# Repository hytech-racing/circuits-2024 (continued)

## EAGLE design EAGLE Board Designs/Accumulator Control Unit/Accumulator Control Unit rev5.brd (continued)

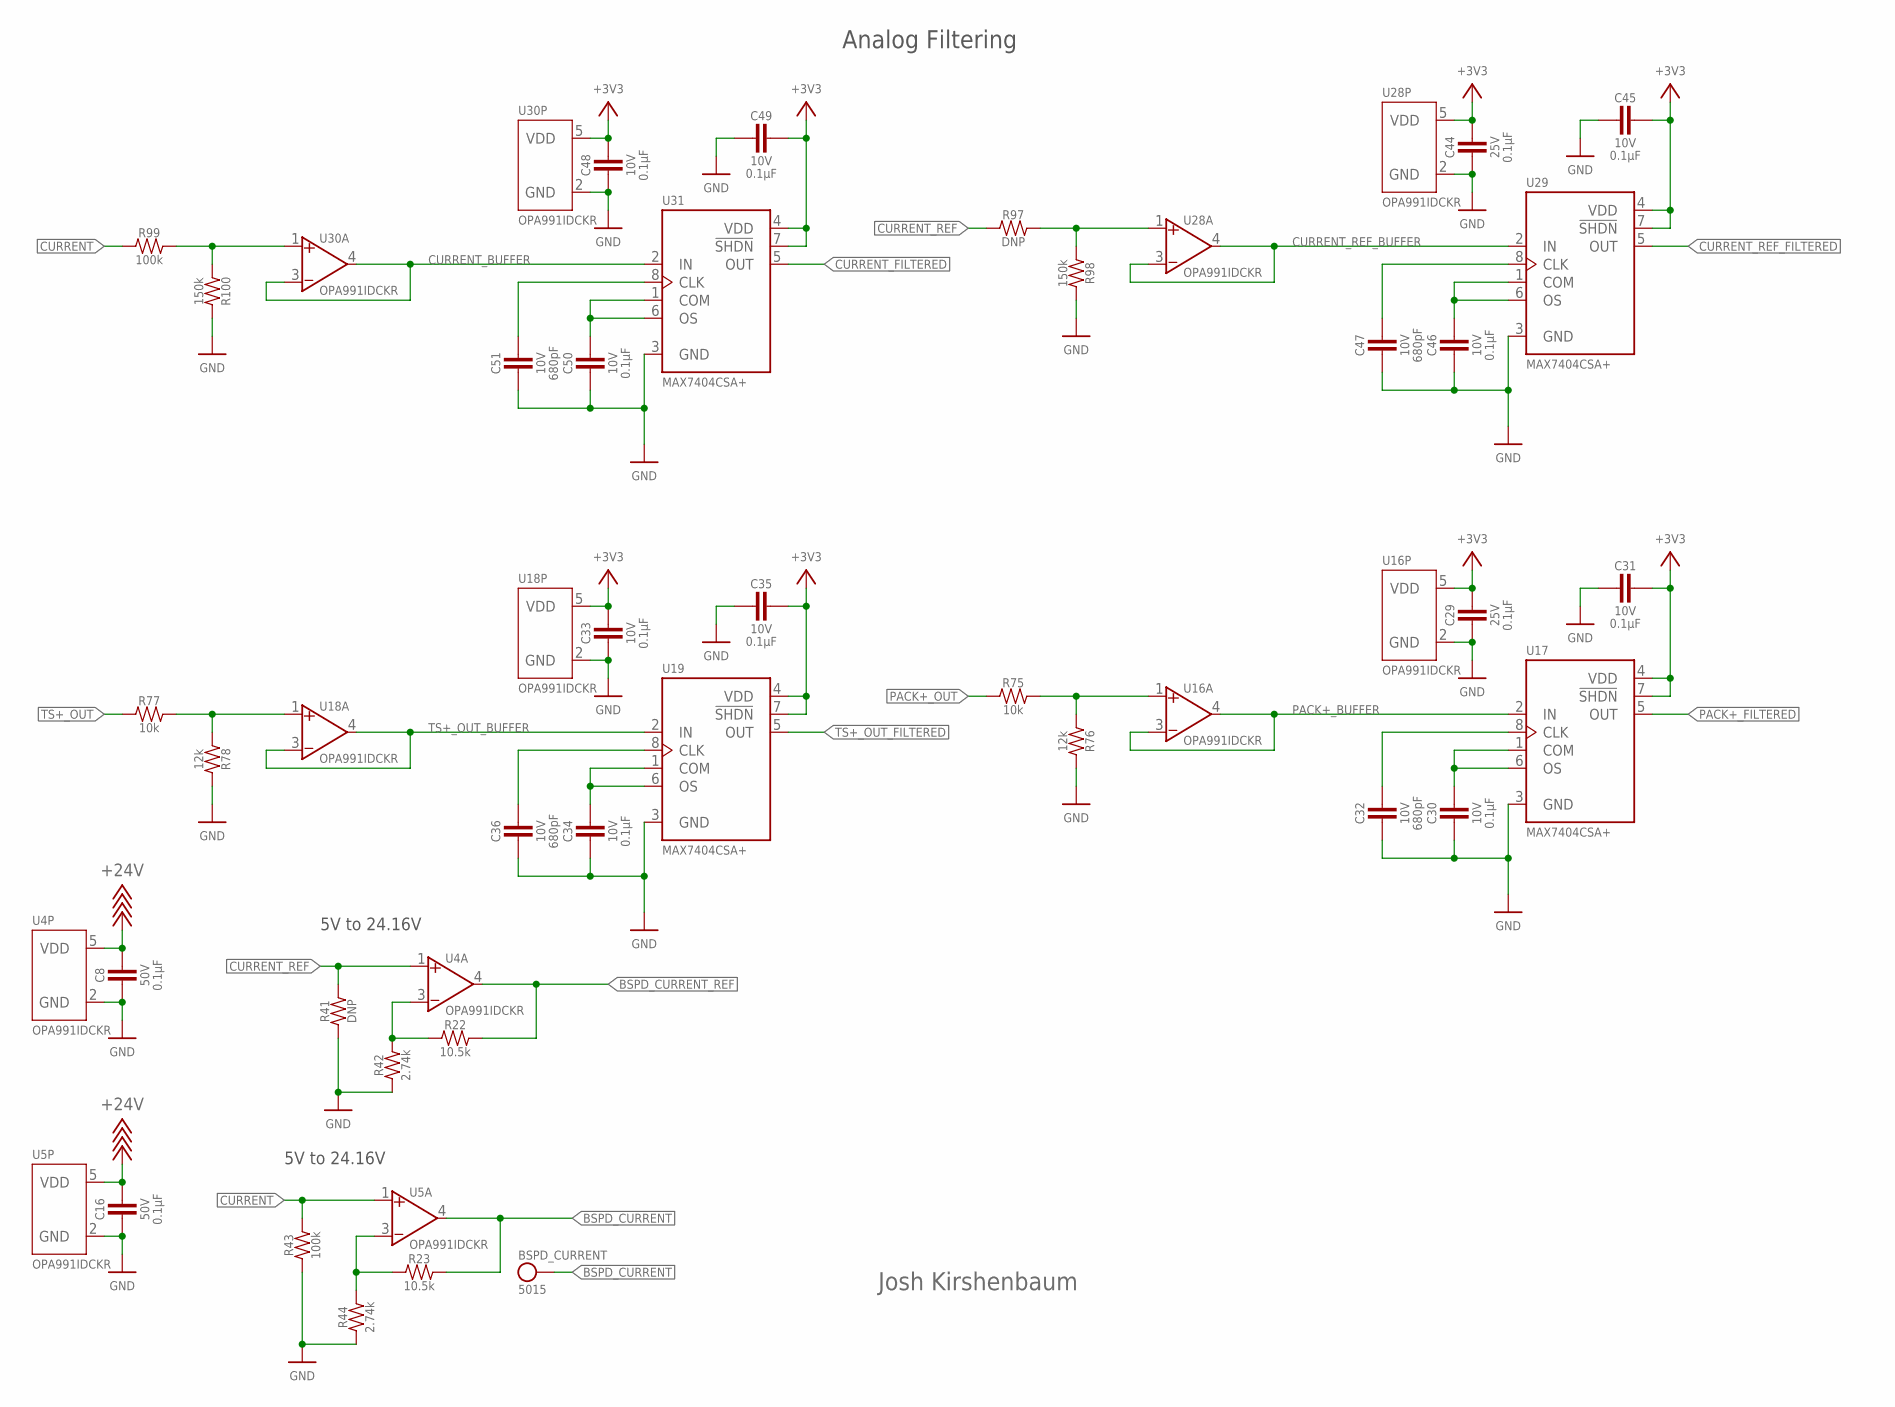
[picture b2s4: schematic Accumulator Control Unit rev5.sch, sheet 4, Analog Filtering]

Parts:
BSPD_CURRENT: TEST_POINT; MICRO_MINIATURE
C8, C16: CAPACITOR_0603_50V_0.1UF; 0603-CAP
C29, C44: CAPACITOR_0603_25V_0.1UF; 0603-CAP
C30, C31, C33, C34, C35, C45, C46, C48, C49, C50: CAPACITOR_0603_10V_0.1UF; 0603-CAP
C32, C36, C47, C51: CAPACITOR_0603_10V_680PF; 0603-CAP
R22, R23: RESISTOR_0603_10.5K; 0603-RES
R41, R97: RESISTOR_0603_DNP; 0603-RES
R42, R44: RESISTOR_0603_2.74K; 0603-RES
R43, R99: RESISTOR_0603_100K; 0603-RES
R75, R77: RESISTOR_0603_10K; 0603-RES
R76, R78: RESISTOR_0603_12K; 0603-RES
R98, R100: RESISTOR_0603_150K; 0603-RES
U4, U5, U16, U18, U28, U30: OPAMP_1_CHANNEL_OPA991; SC-70-5
U17, U19, U29, U31: MAX7404; SOIC-08(NARROW,0.15")

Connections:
+3V3: C29.1, C31.1, C33.1, C35.1, C44.1, C45.1, C48.1, C49.1, U16.5 (VDD), U17.4 (VDD), U17.7 (!SHDN), U18.5 (VDD), U19.4 (VDD), U19.7 (!SHDN), U28.5 (VDD), U29.4 (VDD), U29.7 (!SHDN), U30.5 (VDD), U31.4 (VDD), U31.7 (!SHDN); also elsewhere on the board
+24V: C8.1, C16.1, U4.5 (VDD), U5.5 (VDD); also elsewhere on the board
BSPD_CURRENT: BSPD_CURRENT.1, R23.2, U5.4 (VOUT); also elsewhere on the board
BSPD_CURRENT_REF: R22.2, U4.4 (VOUT); also elsewhere on the board
CURRENT: R43.2, R99.1, U5.1 (VIN+); also elsewhere on the board
CURRENT_BUFFER: U30.3 (VIN-), U30.4 (VOUT), U31.2 (IN)
CURRENT_FILTERED: U31.5 (OUT); also elsewhere on the board
CURRENT_REF: R41.2, R97.1, U4.1 (VIN+); also elsewhere on the board
CURRENT_REF_BUFFER: U28.3 (VIN-), U28.4 (VOUT), U29.2 (IN)
CURRENT_REF_FILTERED: U29.5 (OUT); also elsewhere on the board
GND: C8.2, C16.2, C29.2, C30.2, C31.2, C32.2, C33.2, C34.2, C35.2, C36.2, C44.2, C45.2, C46.2, C47.2, C48.2, C49.2, C50.2, C51.2, R41.1, R42.1, R43.1, R44.1, R76.2, R78.2, R98.2, R100.2, U4.2 (GND), U5.2 (GND), U16.2 (GND), U17.3 (GND), U18.2 (GND), U19.3 (GND), U28.2 (GND), U29.3 (GND), U30.2 (GND), U31.3 (GND); also elsewhere on the board
unnamed: R23.1, R44.2, U5.3 (VIN-)
unnamed: C34.1, U19.1 (COM), U19.6 (OS)
unnamed: R22.1, R42.2, U4.3 (VIN-)
unnamed: C36.1, U19.8 (CLK)
unnamed: R77.2, R78.1, U18.1 (VIN+)
unnamed: C50.1, U31.1 (COM), U31.6 (OS)
unnamed: C51.1, U31.8 (CLK)
unnamed: R99.2, R100.1, U30.1 (VIN+)
unnamed: C46.1, U29.1 (COM), U29.6 (OS)
unnamed: C47.1, U29.8 (CLK)
unnamed: R97.2, R98.1, U28.1 (VIN+)
unnamed: C30.1, U17.1 (COM), U17.6 (OS)
unnamed: C32.1, U17.8 (CLK)
unnamed: R75.2, R76.1, U16.1 (VIN+)
PACK+_BUFFER: U16.3 (VIN-), U16.4 (VOUT), U17.2 (IN)
PACK+_FILTERED: U17.5 (OUT); also elsewhere on the board
PACK+_OUT: R75.1; also elsewhere on the board
TS+_OUT: R77.1; also elsewhere on the board
TS+_OUT_BUFFER: U18.3 (VIN-), U18.4 (VOUT), U19.2 (IN)
TS+_OUT_FILTERED: U19.5 (OUT); also elsewhere on the board

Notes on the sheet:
Josh Kirshenbaum
Analog Filtering
5V to 24.16V

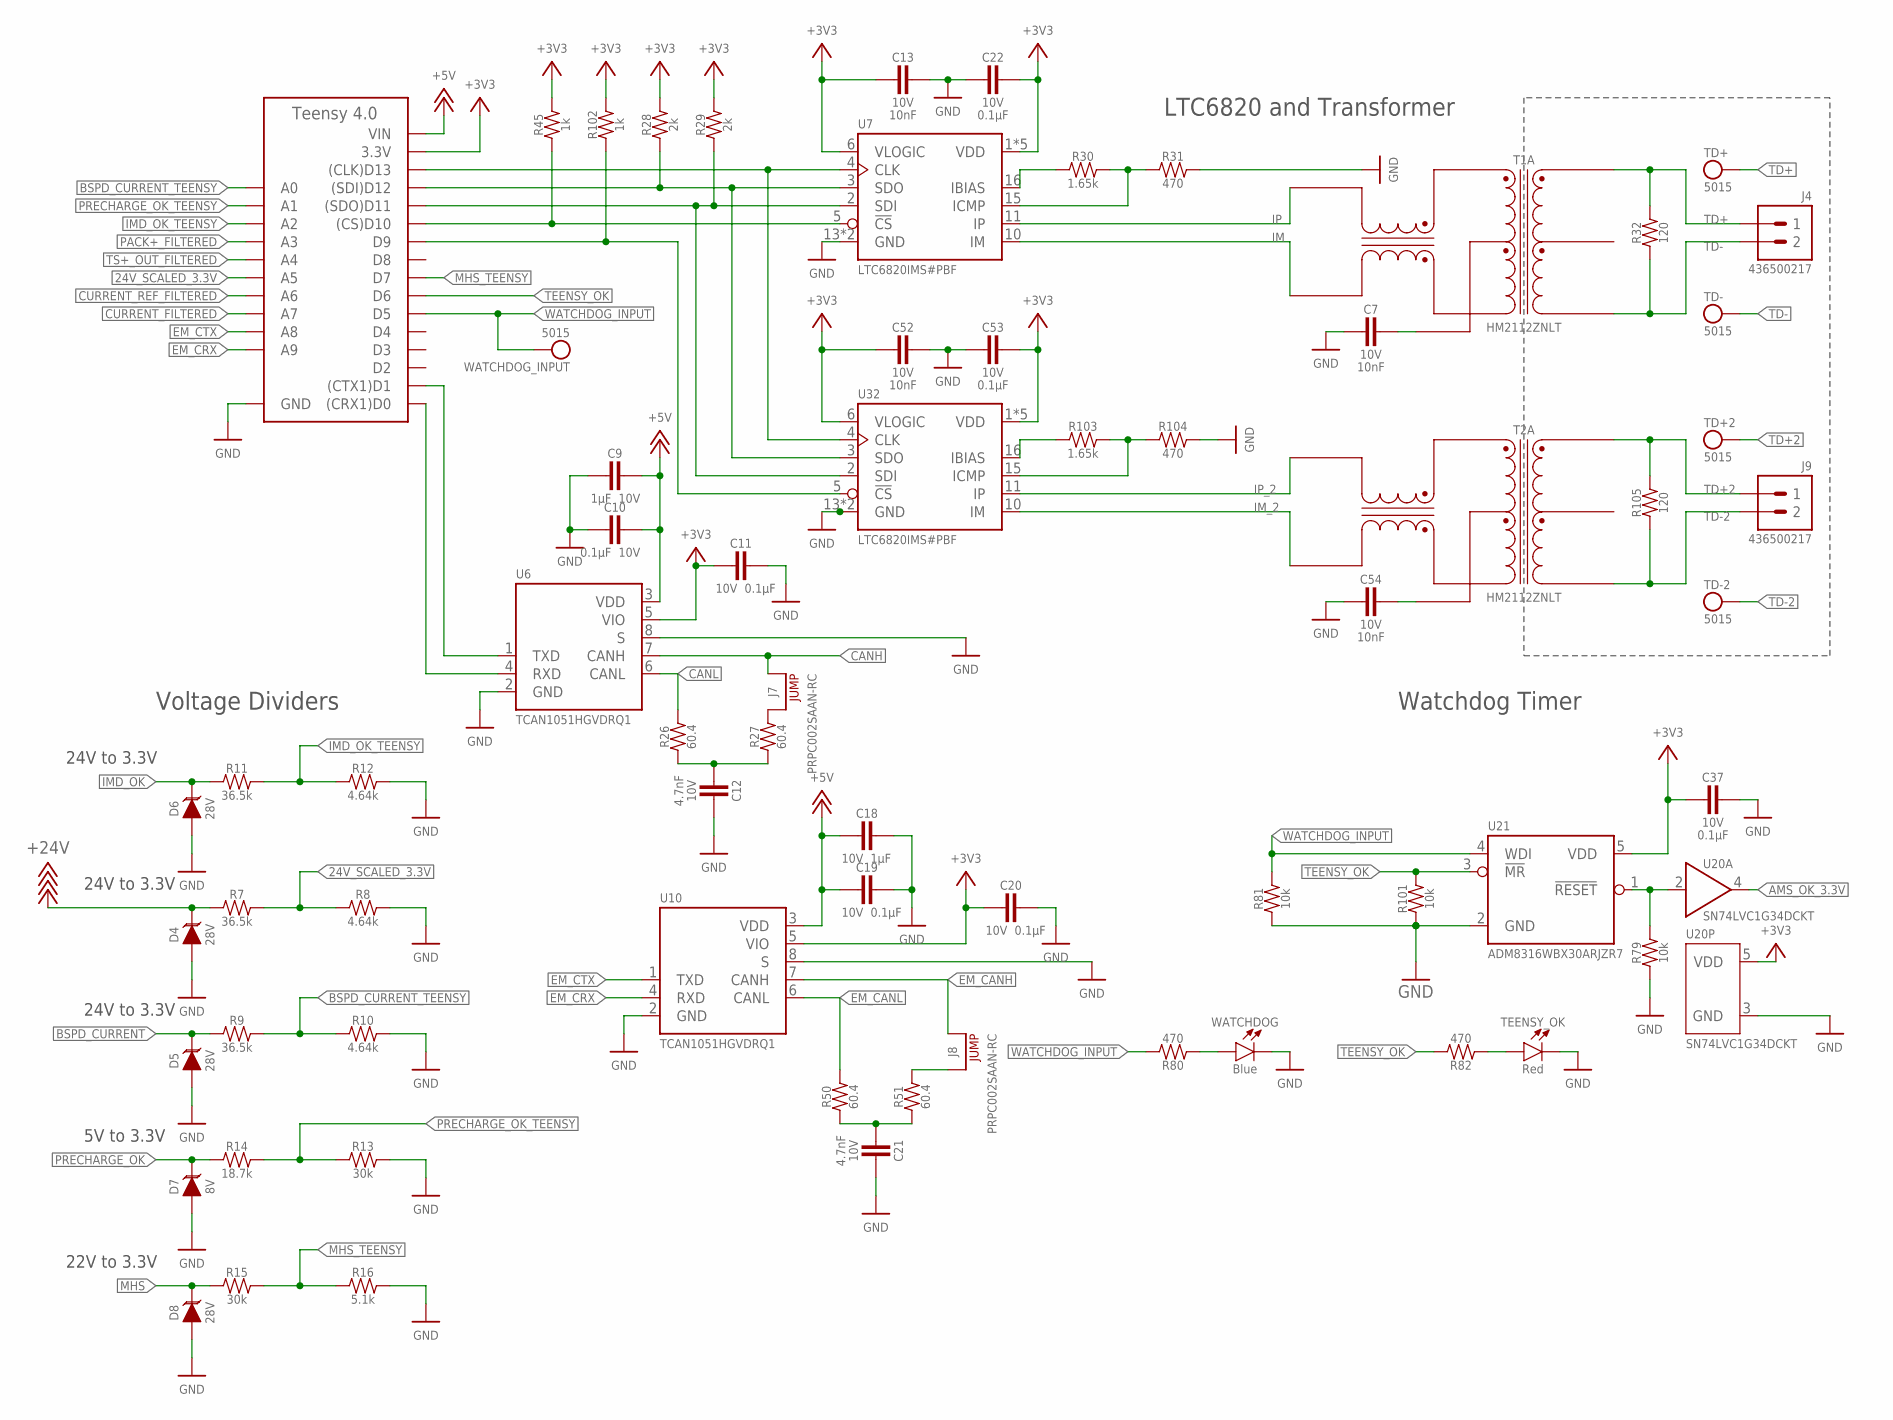
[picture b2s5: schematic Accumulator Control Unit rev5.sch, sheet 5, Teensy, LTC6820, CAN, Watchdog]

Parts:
A3: TEENSY_4.0TH; TEENSY_SHORT
C7, C13, C52, C54: CAPACITOR_0603_10V_10NF; 0603-CAP
C9, C18: CAPACITOR_0603_10V_1UF; 0603-CAP
C10, C11, C19, C20, C22, C37, C53: CAPACITOR_0603_10V_0.1UF; 0603-CAP
C12, C21: CAPACITOR_0603_10V_4.7NF; 0603-CAP
D4, D5, D6, D8: TVS_DO-214AA_28V; DO-214AA
D7: TVS__8V; SOT-23
J4, J9: CONNECTOR-2_MF_T_V_; MOLEX_MICROFIT_PTH_VERTICAL_02_SINGLE
J7, J8: JUMPER__1X02; 1X02
R7, R9, R11: RESISTOR_0603_36.5K; 0603-RES
R8, R10, R12: RESISTOR_0603_4.64K; 0603-RES
R13, R15: RESISTOR_0603_; 0603-RES
R14: RESISTOR_0603_18.7K; 0603-RES
R16: RESISTOR_0603_5.1K; 0603-RES
R26, R27, R50, R51: RESISTOR_0603_60.4; 0603-RES
R28, R29: RESISTOR_0603_2K; 0603-RES
R30, R103: RESISTOR_0603_1.65K; 0603-RES
R31, R80, R82, R104: RESISTOR_0603_470; 0603-RES
R32, R105: RESISTOR_0603_120; 0603-RES
R45, R102: RESISTOR_0603_1K; 0603-RES
R79, R81, R101: RESISTOR_0603_10K; 0603-RES
T1, T2: TRANSFORMER_HM2112ZNLT_AIRGAP; HM2112ZNLT_AIRGAP
TD+, TD+2: TEST_POINT; MICRO_MINIATURE
TD-, TD-2: TEST_POINT; MICRO_MINIATURE
TEENSY_OK: LED_0603_RED; 0603-LED
U6, U10: TCAN1051HQV-Q1; SOIC-08(NARROW,0.15")
U7, U32: LTC6820; MSOP-16
U20: LOGICGATE_BUFFER; SC-70-5
U21: ADM8316WBX30; SOT-23-5
WATCHDOG: LED_0603_BLUE; 0603-LED
WATCHDOG_INPUT: TEST_POINT; MICRO_MINIATURE

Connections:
24V_SCALED_3.3V: A3.D19 (A5), R7.2, R8.1
+3V3: A3.3.3V, C11.2, C13.2, C20.2, C22.1, C37.2, C52.2, C53.1, R28.2, R29.2, R45.2, R102.2, U6.5 (VIO), U7.1 (VDD), U7.6 (VLOGIC), U7.7 (VDD), U7.8 (VDD), U7.9 (VDD), U7.12 (VDD), U10.5 (VIO), U20.5 (VDD), U21.5 (VDD), U32.1 (VDD), U32.6 (VLOGIC), U32.7 (VDD), U32.8 (VDD), U32.9 (VDD), U32.12 (VDD); also elsewhere on the board
+5V: A3.VIN, C9.2, C10.2, C18.2, C19.2, U6.3 (VDD), U10.3 (VDD); also elsewhere on the board
+24V: D4.2 (C), R7.1; also elsewhere on the board
AMS_OK_3.3V: U20.4 (OUT); also elsewhere on the board
BSPD_CURRENT: D5.2 (C), R9.1; also elsewhere on the board
BSPD_CURRENT_TEENSY: A3.D14 (A0), R9.2, R10.1
CANH: J7.1, U6.7 (CANH); also elsewhere on the board
CANH/1.3B: J7.2, R27.2
CANL: R26.2, U6.6 (CANL); also elsewhere on the board
CS_LTC_6820: A3.D10 ((CS)D10), R45.1, U7.5 (!CS)
CURRENT_FILTERED: A3.D21 (A7); also elsewhere on the board
CURRENT_REF_FILTERED: A3.D20 (A6); also elsewhere on the board
EM_CANH: J8.1, U10.7 (CANH); also elsewhere on the board
EM_CANL: R50.2, U10.6 (CANL); also elsewhere on the board
EM_CRX: A3.D23 (A9), U10.4 (RXD)
EM_CTX: A3.D22 (A8), U10.1 (TXD)
GND: A3.AGND/GND (GND), A3.GND, C7.2, C9.1, C10.1, C11.1, C12.1, C13.1, C18.1, C19.1, C20.1, C21.1, C22.2, C37.1, C52.1, C53.2, C54.2, D4.1 (A), D5.1 (A), D6.1 (A), D7.1 (A), D8.1 (A), R8.2, R10.2, R12.2, R13.2, R16.2, R31.2, R79.1, R81.1, R101.1, R104.2, TEENSY_OK.1 (C), U6.2 (GND), U6.8 (S), U7.13 (GND), U7.14 (GND), U10.2 (GND), U10.8 (S), U20.3 (GND), U21.2 (GND), U32.13 (GND), U32.14 (GND), WATCHDOG.1 (C); also elsewhere on the board
IM: T1.10 (TD-), U7.10 (IM)
IMD_OK: D6.2 (C), R11.1; also elsewhere on the board
IMD_OK_TEENSY: A3.D16 (A2), R11.2, R12.1
IM_2: T2.10 (TD-), U32.10 (IM)
IP: T1.12 (TD+), U7.11 (IP)
IP_2: T2.12 (TD+), U32.11 (IP)
MHS: D8.2 (C), R15.1; also elsewhere on the board
MHS_TEENSY: A3.D7, R15.2, R16.1
unnamed: A3.D11 ((SDO)D11), R29.1, U7.2 (SDI), U32.2 (SDI)
unnamed: R79.2, U20.2 (IN), U21.1 (!RESET!)
unnamed: C12.2, R26.1, R27.1
unnamed: A3.D0 ((CRX1)D0), U6.4 (RXD)
unnamed: A3.D1 ((CTX1)D1), U6.1 (TXD)
unnamed: C21.2, R50.1, R51.1
unnamed: J8.2, R51.2
unnamed: R30.1, U7.16 (IBIAS)
unnamed: R30.2, R31.1, U7.15 (ICMP)
unnamed: R103.1, U32.16 (IBIAS)
unnamed: C7.1, T1.11 (TCT)
unnamed: A3.D9, R102.1, U32.5 (!CS)
unnamed: R103.2, R104.1, U32.15 (ICMP)
unnamed: A3.D12 ((SDI)D12), R28.1, U7.3 (SDO), U32.3 (SDO)
unnamed: A3.D13 ((CLK)D13), U7.4 (CLK), U32.4 (CLK)
unnamed: R80.1, WATCHDOG.2 (A)
unnamed: R82.1, TEENSY_OK.2 (A)
unnamed: C54.1, T2.11 (TCT)
PACK+_FILTERED: A3.D17 (A3); also elsewhere on the board
PRECHARGE_OK: D7.3 (C), R14.1; also elsewhere on the board
PRECHARGE_OK_TEENSY: A3.D15 (A1), R13.1, R14.2
TD+: J4.1, R32.2, T1.1 (MX+), TD+.1
TD+2: J9.1, R105.2, T2.1 (MX+), TD+2.1
TD-: J4.2, R32.1, T1.3 (MX-), TD-.1
TD-2: J9.2, R105.1, T2.3 (MX-), TD-2.1
TEENSY_OK: A3.D6, R82.2, R101.2, U21.3 (!MR!)
TS+_OUT_FILTERED: A3.D18 (A4); also elsewhere on the board
WATCHDOG_INPUT: A3.D5, R80.2, R81.2, U21.4 (WDI), WATCHDOG_INPUT.1

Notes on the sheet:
24V to 3.3V
5V to 3.3V
Watchdog Timer
Voltage Dividers
LTC6820 and Transformer
22V to 3.3V

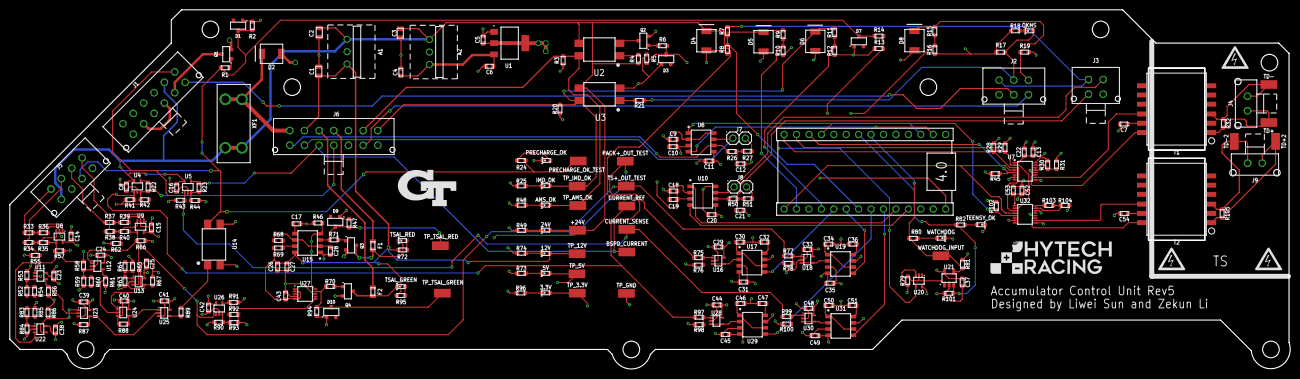
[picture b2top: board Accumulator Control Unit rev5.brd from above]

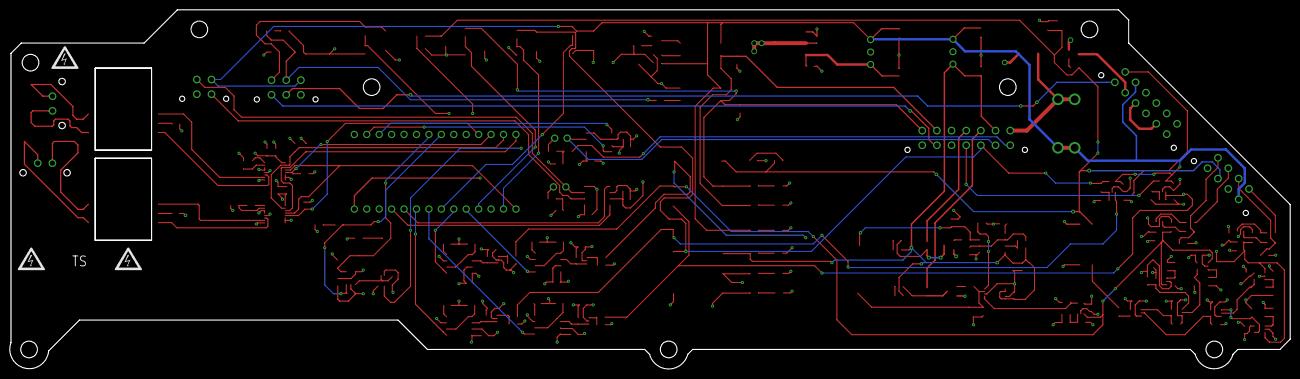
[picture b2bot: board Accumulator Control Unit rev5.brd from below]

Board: 4 copper layers, 261.6 x 73.4 mm, 271 parts (3 on the bottom side), 134 nets.

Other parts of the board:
U$1, U$2, U$4, U$5, U$6, U$12, U$13, U$14: MOUNTING_M3
U$3, U$8, U$10, U$15, U$16, U$17: HV_MEDIUM
U$7: LOGO_GT_MEDIUM
U$9: TS
U$11: LOGO_HYTECH_MEDIUM

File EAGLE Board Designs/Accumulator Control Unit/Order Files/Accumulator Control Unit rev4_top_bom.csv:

Comment,Designator,Footprint,LCSC Part #
ADG1423,U27,MSOP-10,
ADM8316WBX30,U21,SOT-23-5,
CAPACITOR_0603_10V_0.1UF,C10 C11 C14 C15 C19 C20 C22 C23 C24 C25 C30 C31 C33 C34 C35 C37 C38 C39 C40 C41 C42 C45 C46 C48 C49 C50,0603-CAP,
CAPACITOR_0603_10V_1UF,C6 C9 C18,0603-CAP,
CAPACITOR_0603_10V_4.7NF,C12 C21,0603-CAP,
CAPACITOR_0603_10V_4.7UF,C5 C28,0603-CAP,
CAPACITOR_0603_10V_10NF,C7 C13 C17,0603-CAP,
CAPACITOR_0603_10V_680PF,C32 C36 C47 C51,0603-CAP,
CAPACITOR_0603_25V_0.1UF,C26 C29 C44,0603-CAP,
CAPACITOR_0603_25V_1UF,C27 C43,0603-CAP,
CAPACITOR_0603_25V_10UF,C4,0603-CAP,
CAPACITOR_0603_50V_0.1UF,C8 C16,0603-CAP,
CAPACITOR_0805_50V_10UF,C1 C2 C3,0805-CAP,
FUSE_0603_.75A,F1 F2,0603-FUSE,
LED_0603_BLUE,5V WATCHDOG,0603-LED,
LED_0603_GREEN,3.3V AMS_OK TSAL_GREEN,0603-LED,
LED_0603_ORANGE,24V IMD_OK,0603-LED,
LED_0603_RED,12V PRECHARGE_OK TEENSY_OK TSAL_RED,0603-LED,
LED_0603_YELLOW,OKHS,0603-LED,
LM555,U15,SOIC-08(NARROW 0.15"),
LOGICGATE_AND_DCK3,U23 U24 U25,SC-70-5,
LOGICGATE_BUFFER,U20,SC-70-5,
LTC6820,U7,MSOP-16,
MAX7404,U17,SOIC-08(NARROW 0.15"),
MAX7404,U19,SOIC-08(NARROW 0.15"),
MAX7404,U29,SOIC-08(NARROW 0.15"),
MAX7404,U31,SOIC-08(NARROW 0.15"),
OPAMP_1_CHANNEL_OPA991,U4 U5 U8 U9 U11 U12 U13 U16 U18 U22 U26 U28 U30,SC-70-5,
RELAY_SOLIDSTATE_NO_CPC1020NTR,K1,SOP-04,
RELAY_SOLIDSTATE_NO_DIP-4,U2 U3 U14,DIP-4,
RESISTOR_0603_,R13 R15,0603-RES,
RESISTOR_0603_1K,R24 R30 R31 R65 R73 R83 R96,0603-RES,
RESISTOR_0603_1M,R92,0603-RES,
RESISTOR_0603_2.2K,R17 R19,0603-RES,
RESISTOR_0603_2.74K,R42 R44,0603-RES,
RESISTOR_0603_2K,R18 R25 R28 R29 R48 R72 R74 R95,0603-RES,
RESISTOR_0603_3.3K,R49,0603-RES,
RESISTOR_0603_4.64K,R8 R10 R12,0603-RES,
RESISTOR_0603_5.1K,R4 R16 R21,0603-RES,
RESISTOR_0603_5.9K,R54,0603-RES,
RESISTOR_0603_8.66K,R93,0603-RES,
RESISTOR_0603_10,R1 R6 R70 R71,0603-RES,
RESISTOR_0603_10.5K,R22 R23 R33 R34 R37 R38,0603-RES,
RESISTOR_0603_10K,R2 R5 R45 R46 R47 R55 R56 R57 R61 R62 R66 R67 R69 R75 R77 R79 R81 R86 R87 R88 R91 R94 R97 R99 R101,0603-RES,
RESISTOR_0603_11.5K,R53,0603-RES,
RESISTOR_0603_12K,R76 R78 R98 R100,0603-RES,
RESISTOR_0603_13K,R35 R36 R39 R40,0603-RES,
RESISTOR_0603_14K,R63 R84,0603-RES,
RESISTOR_0603_18.7K,R14,0603-RES,
RESISTOR_0603_20K,R3 R20,0603-RES,
RESISTOR_0603_36.5K,R7 R9 R11 R58,0603-RES,
RESISTOR_0603_43K,R68,0603-RES,
RESISTOR_0603_60.4,R26 R27 R50 R51,0603-RES,
RESISTOR_0603_73.2K,R90,0603-RES,
RESISTOR_0603_100K,R41 R43,0603-RES,
RESISTOR_0603_120,R32,0603-RES,
RESISTOR_0603_330K,R59,0603-RES,
RESISTOR_0603_470,R80 R82 R89,0603-RES,
RESISTOR_0603_DNP,R52 R60 R64 R85,0603-RES,
TCAN1051HQV-Q1,U6,SOIC-08(NARROW 0.15"),
TCAN1051HQV-Q1,U10,SOIC-08(NARROW 0.15"),
TEST_POINT,BSPD_CURRENT CURRENT_REF CURRENT_SENSE PACK+_OUT_TEST PRECHARGE_OK_TEST TD+ TD-,MICRO_MINIATURE,
TEST_POINT,TP_3.3V TP_5V TP_12V TP_24V,5015,
TEST_POINT,TP_AMS_OK,MICRO_MINIATURE,
TEST_POINT,TP_GND,5015,
TEST_POINT,TP_IMD_OK TP_TSAL_GREEN TP_TSAL_RED TS+_OUT_TEST WATCHDOG_INPUT,MICRO_MINIATURE,
TRANSFORMER_HM2112ZNLT_AIRGAP,T1,HM2112ZNLT_AIRGAP,
TRANSISTOR_N_MOS__PMV15ENEA,Q1 Q2 Q3 Q4,SOT-23,
TVS_8V,D1 D3 D7,SOT-23,
TVS_15V,D9 D10,SOT-23,
TVS_28VDO-214AA,D4 D5 D6 D8,DO-214AA,
TVS_30VDO-214AA,D2,DO-214AA,
VOLTAGE_REGULATOR_SOT-223_3.3V,U1,SOT-223,
